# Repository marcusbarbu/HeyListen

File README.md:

# Hey Listen!

Everyone's favorite helper... psyche

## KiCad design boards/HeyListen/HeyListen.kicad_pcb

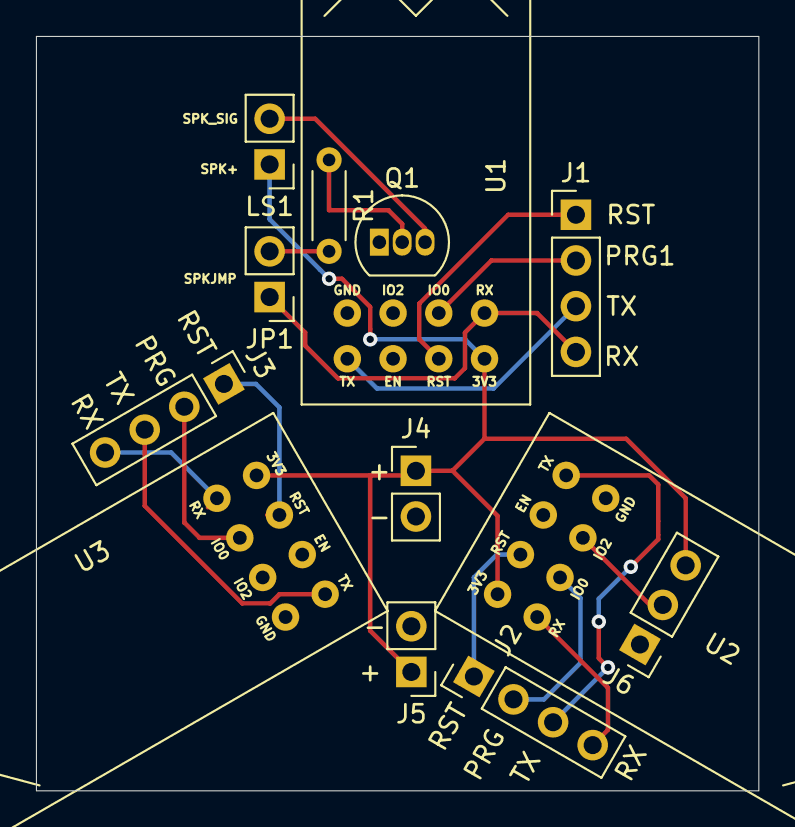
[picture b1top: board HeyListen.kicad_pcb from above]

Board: 2 copper layers, 40.1 x 41.9 mm, 13 parts (0 on the bottom side), 18 nets.

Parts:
J1, J2, J3: Conn_01x04; PinHeader_1x04_P2.54mm_Vertical
J4, J5: Conn_01x02; PinHeader_1x02_P2.54mm_Vertical
J6: Conn_01x03; PinHeader_1x03_P2.54mm_Vertical
JP1: Jumper_2_Open; PinHeader_1x02_P2.54mm_Vertical
LS1: Speaker; PinHeader_1x02_P2.54mm_Vertical
Q1: 2N3904; TO-92_Inline
R1: R; R_Axial_DIN0204_L3.6mm_D1.6mm_P5.08mm_Horizontal
U1, U2, U3: ESP-01

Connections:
/GND: J4.2, J5.2, J6.1, Q1.1, U1.7, U2.7, U3.7
/I2S: JP1.2, R1.2
/LEDSIG: J6.2, U2.6
/PRG1: J1.2, U1.5
/PRG2: J2.2, U2.5
/PRG3: J3.2, U3.5
/RST1: J1.1, U1.2
/RST2: J2.1, U2.2
/RST3: J3.1, U3.2
/RX1: J1.4, JP1.1, U1.4
/RX2: J2.4, U2.4
/RX3: J3.4, U3.4
/TX1: J1.3, U1.0
/TX2: J2.3, U2.0
/TX3: J3.3, U3.0
/V3P3: J4.1, J5.1, J6.3, LS1.1, U1.3, U2.3, U3.3
unnamed: LS1.2, Q1.3
unnamed: Q1.2, R1.1

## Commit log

2021-10-17 initial commit: Contains test fixture code, first likely version of PCB design
2021-10-18 Fixed a disconnected GND
